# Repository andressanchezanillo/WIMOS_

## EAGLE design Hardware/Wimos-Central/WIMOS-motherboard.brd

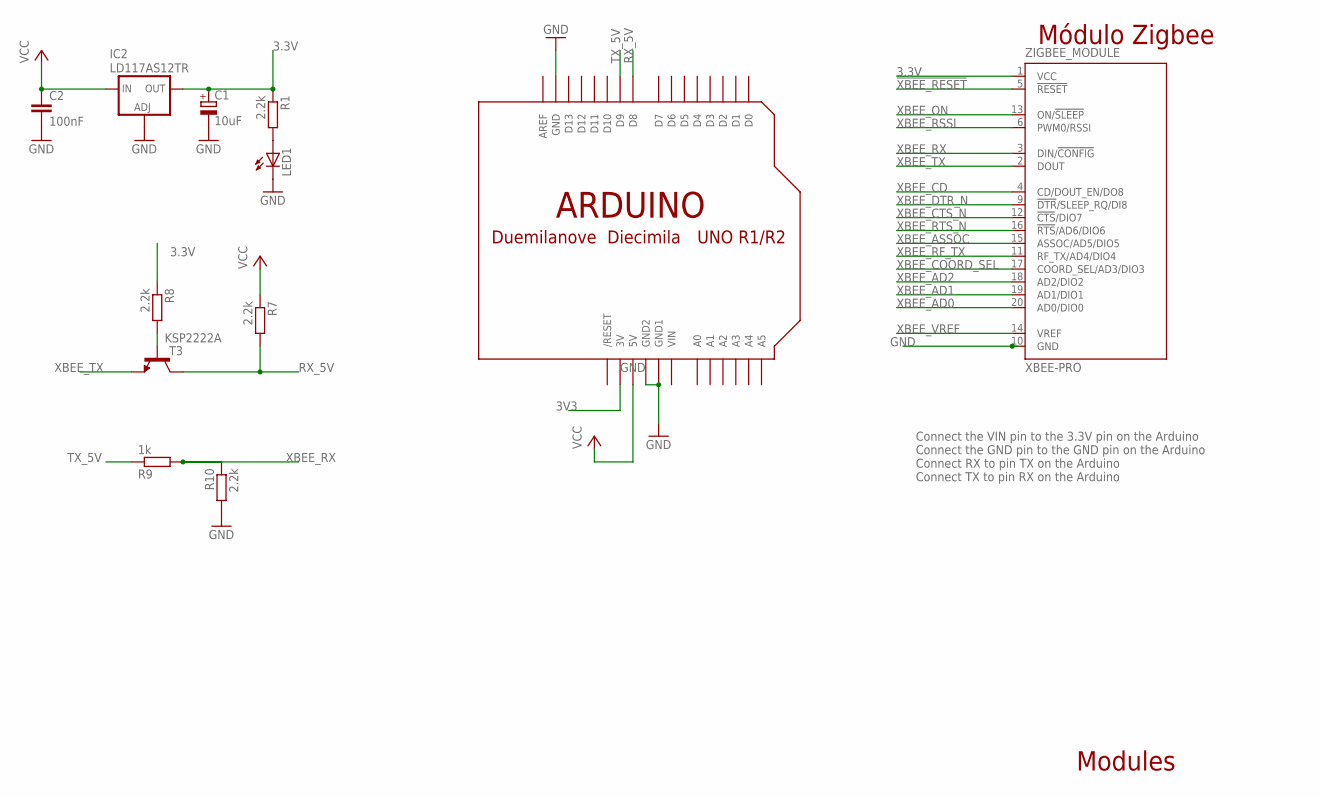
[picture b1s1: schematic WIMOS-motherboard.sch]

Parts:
C1: 10uF; 153CLV-0810
C2: 100nF; C0805K
IC2: LD117AS12TR; SOT223
LED1: LED5MM
R1: 2.2k; R0805
R7, R8, R10: 2.2k; 0204/5
R9: 1k; 0204/5
T3: KSP2222A; TO92-CBE
U$1: ARDUINO-NODIM
ZIGBEE_MODULE: XBEE-PRO

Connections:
3.3V: C1.+, IC2.4 (OUT), R1.1, R8.1, ZIGBEE_MODULE.1 (VCC)
3V3: U$1.3V
!XBEE_RESET: ZIGBEE_MODULE.5 (!RESET)
GND: C1.-, C2.2, IC2.1 (ADJ), LED1.K (C), R10.2, U$1.GND, U$1.GND1, U$1.GND2, ZIGBEE_MODULE.10 (GND)
unnamed: LED1.A, R1.2
unnamed: R8.2, T3.B
RX_5V: R7.2, T3.C, U$1.D8
TX_5V: R9.1, U$1.D9
VCC: C2.1, IC2.3 (IN), R7.1, U$1.5V
VIN: U$1.VIN
XBEE_AD0: ZIGBEE_MODULE.20 (AD0/DIO0)
XBEE_AD1: ZIGBEE_MODULE.19 (AD1/DIO1)
XBEE_AD2: ZIGBEE_MODULE.18 (AD2/DIO2)
XBEE_ASSOC: ZIGBEE_MODULE.15 (ASSOC/AD5/DIO5)
XBEE_CD: ZIGBEE_MODULE.4 (CD/DOUT_EN/DO8)
XBEE_COORD_SEL: ZIGBEE_MODULE.17 (COORD_SEL/AD3/DIO3)
XBEE_CTS_N: ZIGBEE_MODULE.12 (!CTS!/DIO7)
XBEE_DTR_N: ZIGBEE_MODULE.9 (!DTR!/SLEEP_RQ/DI8)
XBEE_ON: ZIGBEE_MODULE.13 (ON/!SLEEP)
XBEE_RF_TX: ZIGBEE_MODULE.11 (RF_TX/AD4/DIO4)
XBEE_RSSI: ZIGBEE_MODULE.6 (PWM0/RSSI)
XBEE_RTS_N: ZIGBEE_MODULE.16 (!RTS!/AD6/DIO6)
XBEE_RX: R9.2, R10.1, ZIGBEE_MODULE.3 (DIN/!CONFIG)
XBEE_TX: T3.E, ZIGBEE_MODULE.2 (DOUT)
XBEE_VREF: ZIGBEE_MODULE.14 (VREF)

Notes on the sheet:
Modules
Connect the VIN pin to the 3.3V pin on the Arduino Connect the GND pin to the GND pin on the Arduino Connect RX to pin TX on the Arduino Connect TX to pin RX on the Arduino
Módulo Zigbee

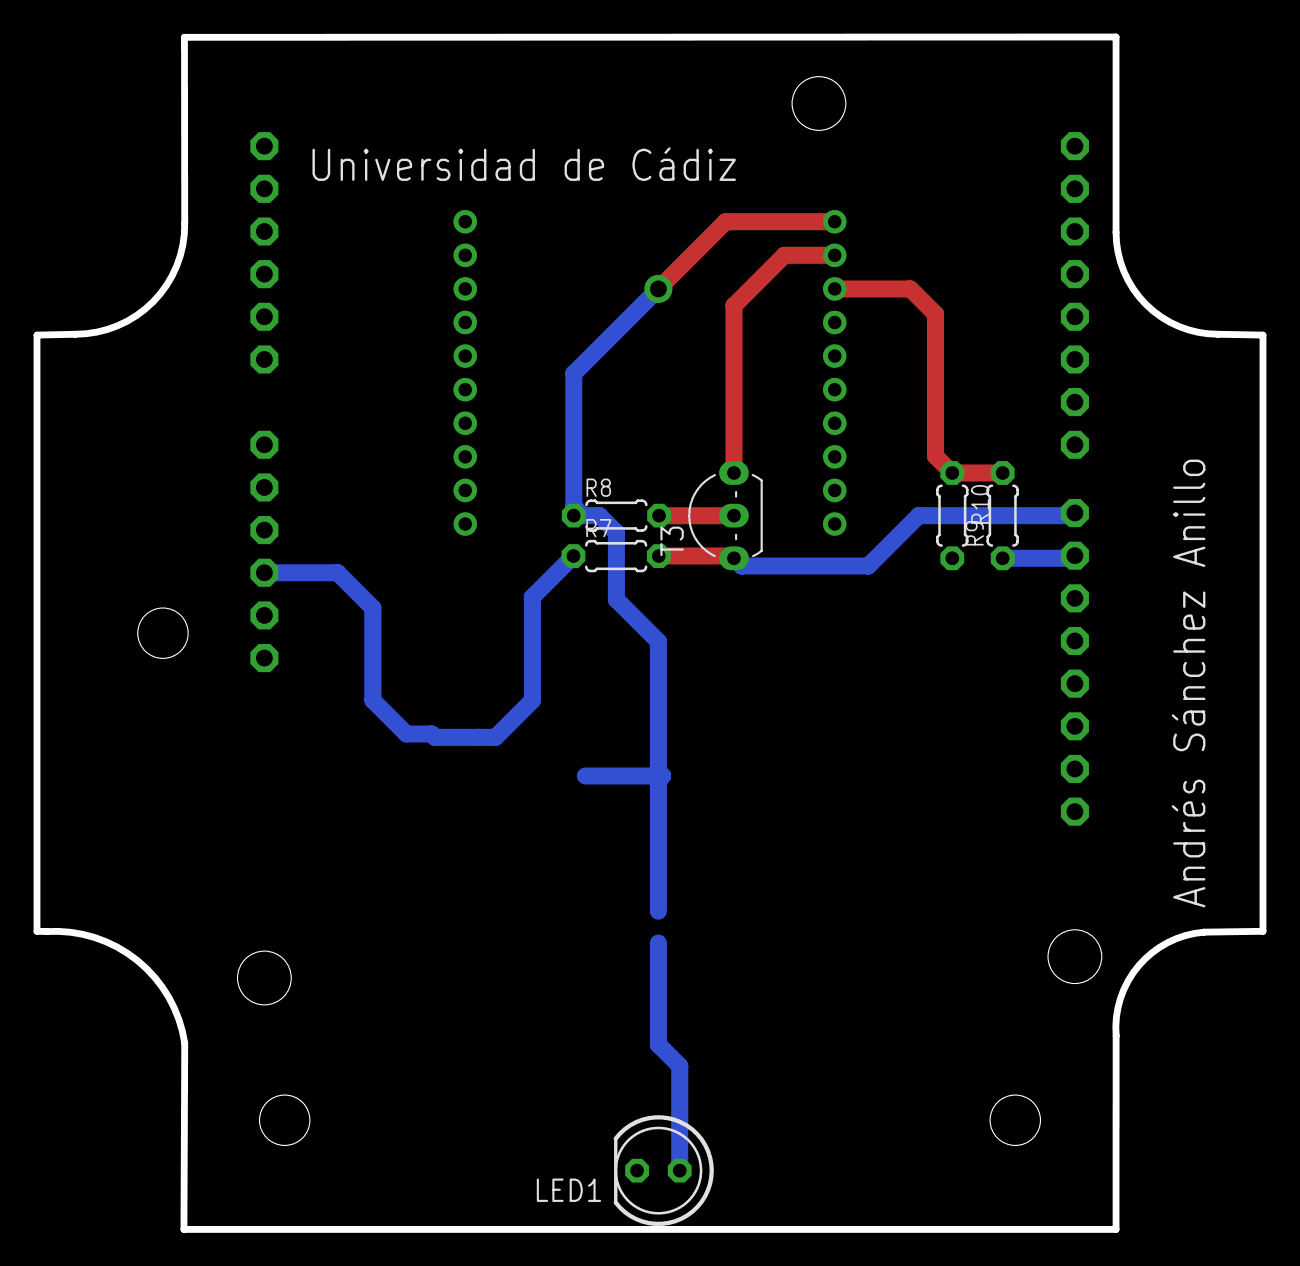
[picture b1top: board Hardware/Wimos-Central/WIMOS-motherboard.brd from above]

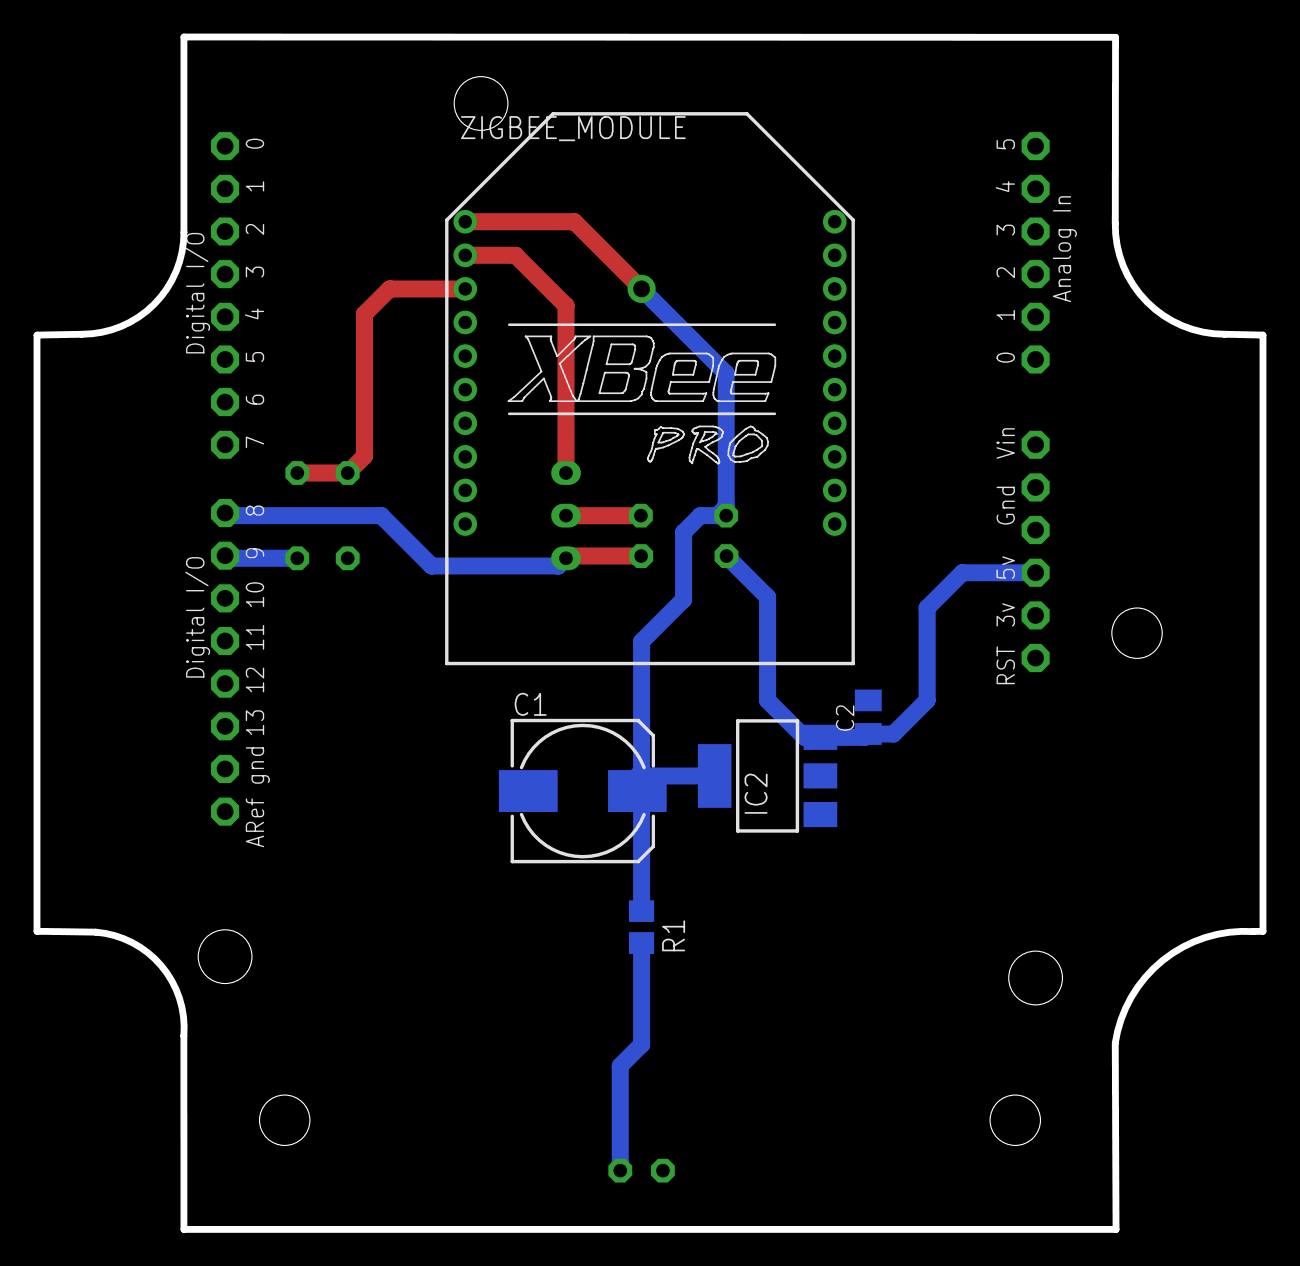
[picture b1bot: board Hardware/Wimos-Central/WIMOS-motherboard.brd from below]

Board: 2 copper layers, 73.0 x 71.0 mm, 12 parts (6 on the bottom side), 9 nets.

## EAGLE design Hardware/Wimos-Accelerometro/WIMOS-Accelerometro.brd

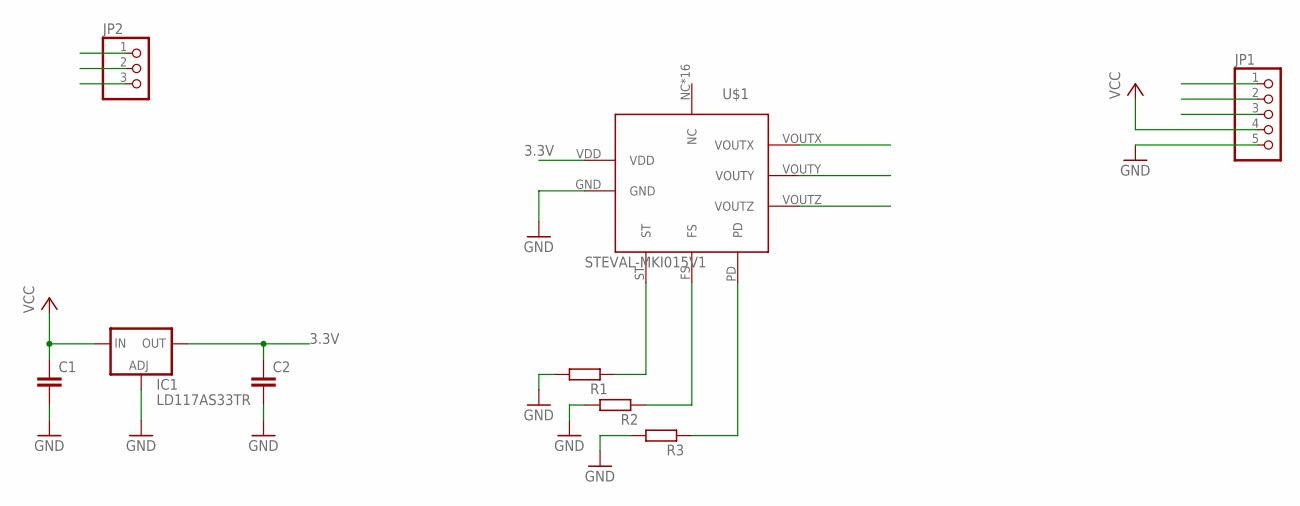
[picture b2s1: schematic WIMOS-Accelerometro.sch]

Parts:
C1, C2: C-EUC0805; C0805
IC1: LD117AS33TR; SOT223
JP1: PINHD-1X5; 1X05
JP2: PINHD-1X3; 1X03
R1, R2, R3: R-EU_R0805; R0805
U$1: STEVAL-MKI015V1

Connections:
3.3V: C2.1, IC1.4 (OUT), U$1.VDD
FS: JP2.2, R2.1, U$1.FS
GND: C1.2, C2.2, IC1.1 (ADJ), JP1.5, R1.2, R2.2, R3.2, U$1.GND
PD: JP2.3, R3.1, U$1.PD
ST: JP2.1, R1.1, U$1.ST
VCC: C1.1, IC1.3 (IN), JP1.4
VOUTX: JP1.1, U$1.VOUTX
VOUTY: JP1.2, U$1.VOUTY
VOUTZ: JP1.3, U$1.VOUTZ

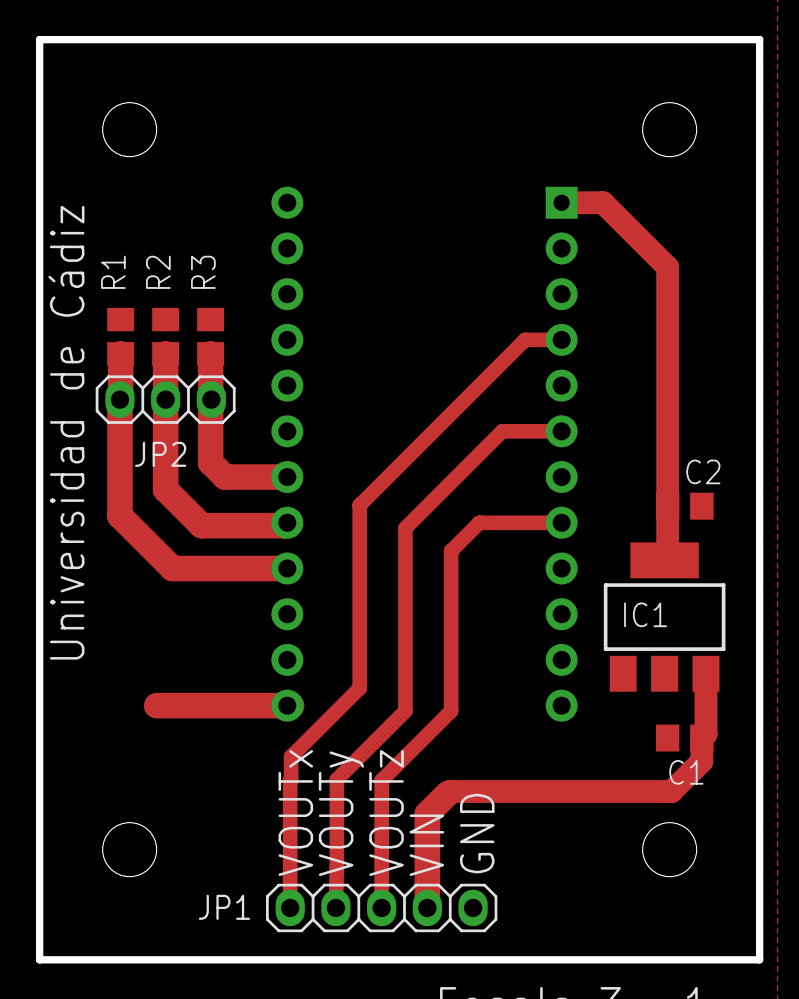
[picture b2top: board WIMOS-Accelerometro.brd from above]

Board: 2 copper layers, 40.0 x 51.1 mm, 9 parts (1 on the bottom side), 9 nets.

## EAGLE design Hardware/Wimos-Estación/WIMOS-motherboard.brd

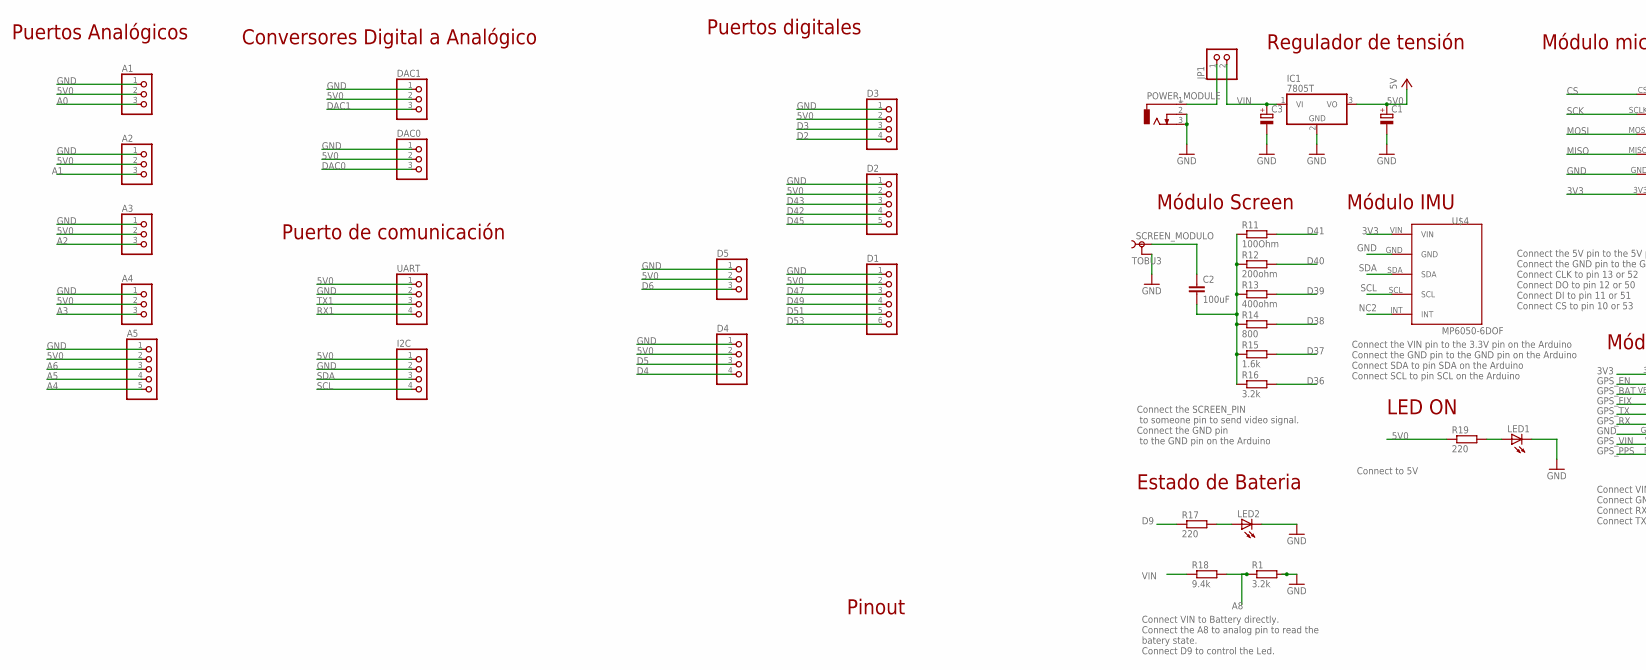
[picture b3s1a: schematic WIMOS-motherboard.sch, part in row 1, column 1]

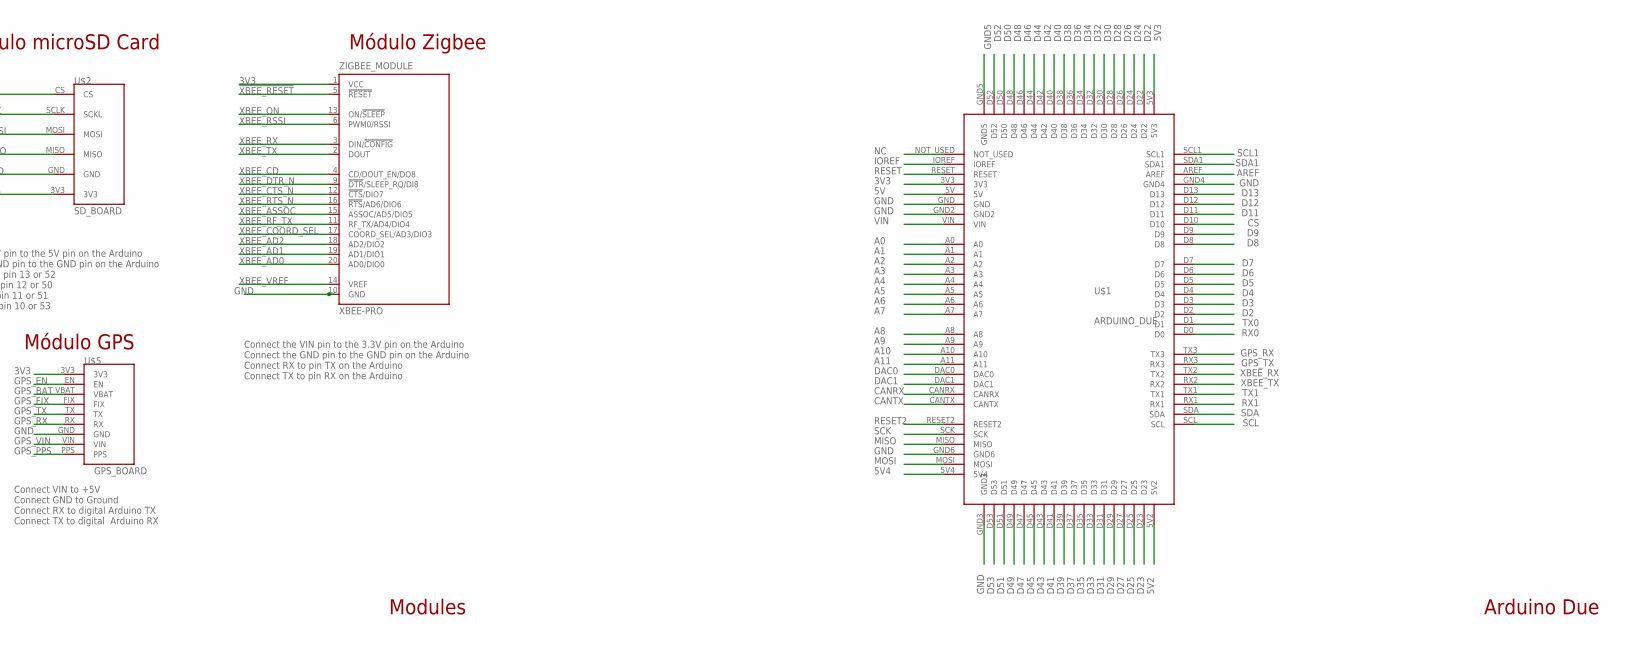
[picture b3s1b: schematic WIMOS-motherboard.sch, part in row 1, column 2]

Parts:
A1, A2, A3, A4: PINHD-1X3/90; 1X03/90
A5: PINHD-1X5/90; 1X05/90
C1, C3: CPOL-EU153CLV-0810; 153CLV-0810
C2: 100uF; C025-025X050
D1: PINHD-1X6/90; 1X06/90
D2: PINHD-1X5/90; 1X05/90
D3, D4: PINHD-1X4/90; 1X04/90
D5: PINHD-1X3/90; 1X03/90
DAC0, DAC1: PINHD-1X3/90; 1X03/90
I2C: PINHD-1X4/90; 1X04/90
IC1: 7805T; TO220H
JP1: PINHD-1X2; 1X02
LED1, LED2: LED_E; LED_1206
POWER_MODULE: DCJ0303
R1, R16: 3.2k; R0805
R11: 100Ohm; R0805
R12: 200ohm; R0805
R13: 400ohm; R0805
R14: 800; R0805
R15: 1.6k; R0805
R17, R19: 220; R0805
R18: 9.4k; R0805
SCREEN_MODULO: TOBU3
U$1: ARDUINO_DUE
U$2: SD_BOARD
U$4: MP6050-6DOF
U$5: GPS_BOARD; SD_BOARD
UART: PINHD-1X4/90; 1X04/90
ZIGBEE_MODULE: XBEE-PRO

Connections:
3V3: U$1.3V3, U$2.3V3, U$4.VIN, U$5.3V3, ZIGBEE_MODULE.1 (VCC)
5V: U$1.5V
5V0: A1.2, A2.2, A3.2, A4.2, A5.2, C1.+, D1.2, D2.2, D3.2, D4.2, D5.2, DAC0.2, DAC1.2, I2C.1, IC1.3 (VO), R19.1, UART.1
5V2: U$1.5V2
5V3: U$1.5V3
5V4: U$1.5V4
!XBEE_RESET: ZIGBEE_MODULE.5 (!RESET)
A0: A1.3, U$1.A0
A1: A2.3, U$1.A1
A2: A3.3, U$1.A2
A3: A4.3, U$1.A3
A4: A5.5, U$1.A4
A5: A5.4, U$1.A5
A6: A5.3, U$1.A6
A7: U$1.A7
A8: R1.1, R18.2, U$1.A8
A9: U$1.A9
A10: U$1.A10
A11: U$1.A11
AREF: U$1.AREF
CANRX: U$1.CANRX
CANTX: U$1.CANTX
CS: U$1.D10, U$2.CS
D2: D3.4, U$1.D2
D3: D3.3, U$1.D3
D4: D4.4, U$1.D4
D5: D4.3, U$1.D5
D6: D5.3, U$1.D6
D7: U$1.D7
D8: U$1.D8
D9: R17.1, U$1.D9
D11: U$1.D11
D12: U$1.D12
D13: U$1.D13
D22: U$1.D22
D23: U$1.D23
D24: U$1.D24
D25: U$1.D25
D26: U$1.D26
D27: U$1.D27
D28: U$1.D28
D29: U$1.D29
D30: U$1.D30
D31: U$1.D31
D32: U$1.D32
D33: U$1.D33
D34: U$1.D34
D35: U$1.D35
D36: R16.2, U$1.D36
D37: R15.2, U$1.D37
D38: R14.2, U$1.D38
D39: R13.2, U$1.D39
D40: R12.2, U$1.D40
D41: R11.2, U$1.D41
D42: D2.4, U$1.D42
D43: D2.3, U$1.D43
D44: U$1.D44
D45: D2.5, U$1.D45
D46: U$1.D46
D47: D1.3, U$1.D47
D48: U$1.D48
D49: D1.4, U$1.D49
D50: U$1.D50
D51: D1.5, U$1.D51
D52: U$1.D52
D53: D1.6, U$1.D53
DAC0: DAC0.3, U$1.DAC0
DAC1: DAC1.3, U$1.DAC1
GND: A1.1, A2.1, A3.1, A4.1, A5.1, C1.-, C3.-, D1.1, D2.1, D3.1, D4.1, D5.1, DAC0.1, DAC1.1, I2C.2, IC1.2 (GND), LED1.C, LED2.C, POWER_MODULE.2, POWER_MODULE.3, R1.2, SCREEN_MODULO.2, SCREEN_MODULO.2@1 (2), SCREEN_MODULO.2@2 (2), U$1.GND, U$1.GND2, U$1.GND3, U$1.GND4, U$1.GND6, U$2.GND, U$4.GND, U$5.GND, UART.2, ZIGBEE_MODULE.10 (GND)
GND5: U$1.GND5
GPS_BAT: U$5.VBAT
GPS_EN: U$5.EN
GPS_FIX: U$5.FIX
GPS_PPS: U$5.PPS
GPS_RX: U$1.TX3, U$5.RX
GPS_TX: U$1.RX3, U$5.TX
GPS_VIN: U$5.VIN
IOREF: U$1.IOREF
MISO: U$1.MISO, U$2.MISO
MOSI: U$1.MOSI, U$2.MOSI
unnamed: LED1.A, R19.2
unnamed: C2.1, SCREEN_MODULO.1
unnamed: JP1.1, POWER_MODULE.1
unnamed: LED2.A, R17.2
unnamed: C2.2, R11.1, R12.1, R13.1, R14.1, R15.1, R16.1
NC: U$1.NOT_USED
NC2: U$4.INT
RESET: U$1.RESET
RESET2: U$1.RESET2
RX0: U$1.D0
RX1: U$1.RX1, UART.4
SCK: U$1.SCK, U$2.SCLK (SCKL)
SCL: I2C.4, U$1.SCL, U$4.SCL
SCL1: U$1.SCL1
SDA: I2C.3, U$1.SDA, U$4.SDA
SDA1: U$1.SDA1
TX0: U$1.D1
TX1: U$1.TX1, UART.3
VIN: C3.+, IC1.1 (VI), JP1.2, R18.1, U$1.VIN
XBEE_AD0: ZIGBEE_MODULE.20 (AD0/DIO0)
XBEE_AD1: ZIGBEE_MODULE.19 (AD1/DIO1)
XBEE_AD2: ZIGBEE_MODULE.18 (AD2/DIO2)
XBEE_ASSOC: ZIGBEE_MODULE.15 (ASSOC/AD5/DIO5)
XBEE_CD: ZIGBEE_MODULE.4 (CD/DOUT_EN/DO8)
XBEE_COORD_SEL: ZIGBEE_MODULE.17 (COORD_SEL/AD3/DIO3)
XBEE_CTS_N: ZIGBEE_MODULE.12 (!CTS!/DIO7)
XBEE_DTR_N: ZIGBEE_MODULE.9 (!DTR!/SLEEP_RQ/DI8)
XBEE_ON: ZIGBEE_MODULE.13 (ON/!SLEEP)
XBEE_RF_TX: ZIGBEE_MODULE.11 (RF_TX/AD4/DIO4)
XBEE_RSSI: ZIGBEE_MODULE.6 (PWM0/RSSI)
XBEE_RTS_N: ZIGBEE_MODULE.16 (!RTS!/AD6/DIO6)
XBEE_RX: U$1.TX2, ZIGBEE_MODULE.3 (DIN/!CONFIG)
XBEE_TX: U$1.RX2, ZIGBEE_MODULE.2 (DOUT)
XBEE_VREF: ZIGBEE_MODULE.14 (VREF)

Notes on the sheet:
Connect the 5V pin to the 5V pin on the Arduino Connect the GND pin to the GND pin on the Arduino Connect CLK to pin 13 or 52 Connect DO to pin 12 or 50 Connect DI to pin 11 or 51 Connect CS to pin 10 or 53
Connect the VIN pin to the 3.3V pin on the Arduino Connect the GND pin to the GND pin on the Arduino Connect SDA to pin SDA on the Arduino Connect SCL to pin SCL on the Arduino
Connect VIN to +5V Connect GND to Ground Connect RX to digital Arduino TX Connect TX to digital Arduino RX
Connect the VIN pin to the 3.3V pin on the Arduino Connect the GND pin to the GND pin on the Arduino Connect RX to pin TX on the Arduino Connect TX to pin RX on the Arduino
Modules
Arduino Due
Pinout
Regulador de tensión
Módulo microSD Card
Módulo Zigbee
Módulo IMU
Módulo Screen
Módulo GPS
Connect the SCREEN_PIN to someone pin to send video signal. Connect the GND pin to the GND pin on the Arduino
Puertos Analógicos
Conversores Digital a Analógico
Puerto de comunicación
Puertos digitales
Estado de Bateria
LED ON
Connect to 5V
Connect VIN to Battery directly. Connect the A8 to analog pin to read the batery state. Connect D9 to control the Led.

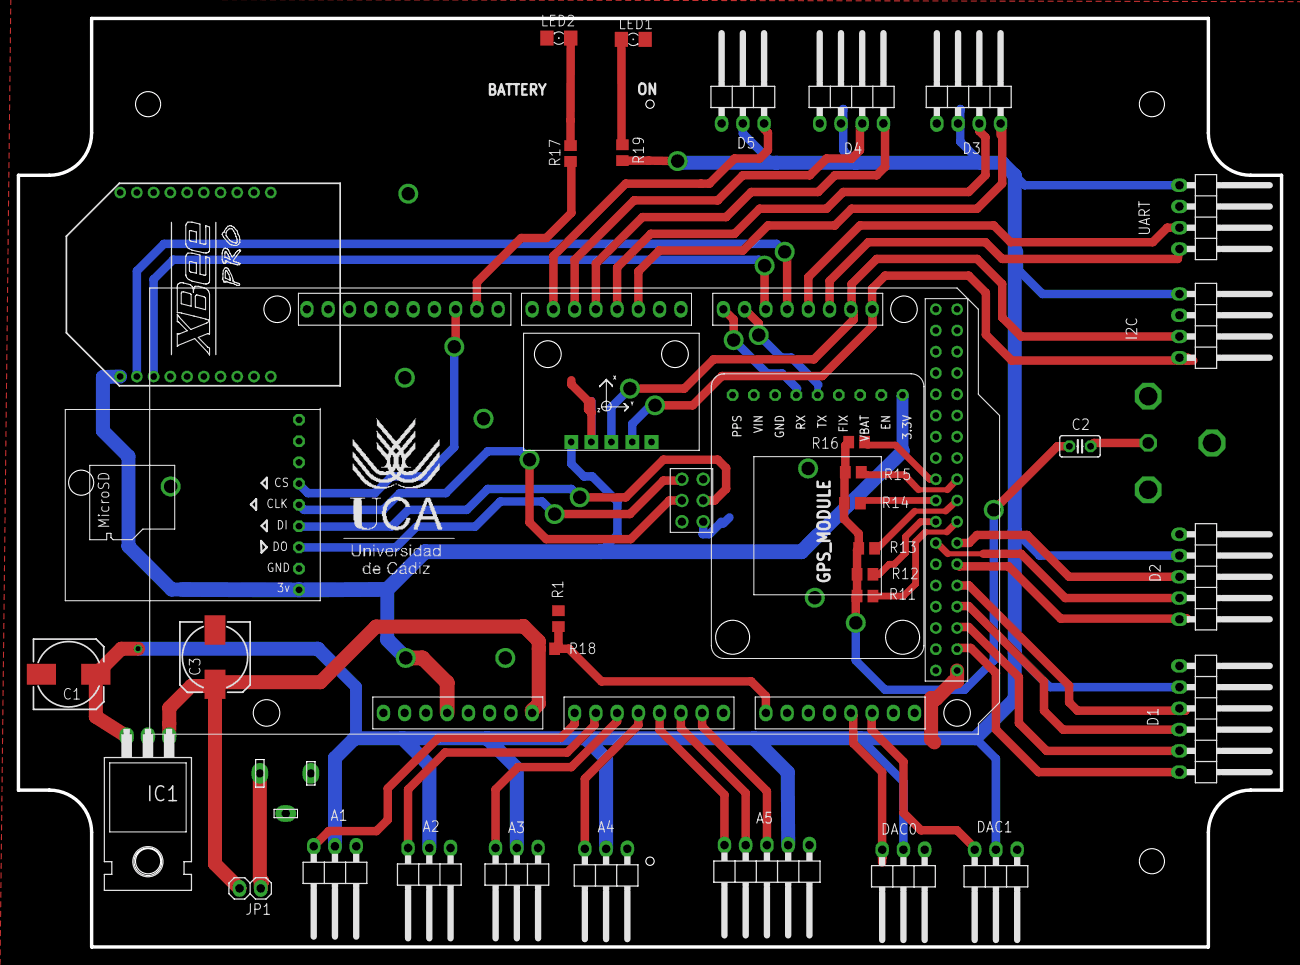
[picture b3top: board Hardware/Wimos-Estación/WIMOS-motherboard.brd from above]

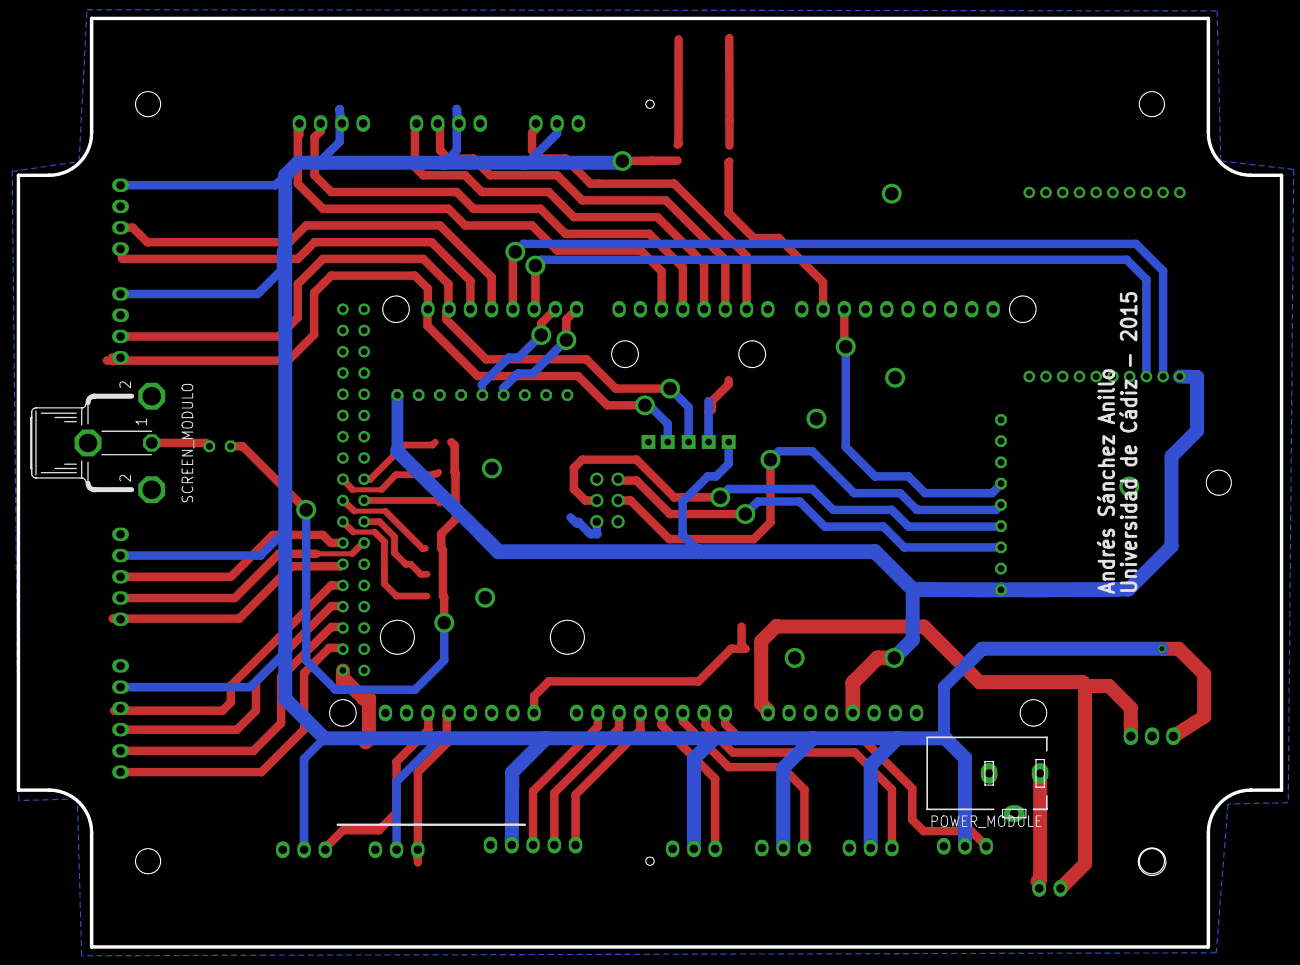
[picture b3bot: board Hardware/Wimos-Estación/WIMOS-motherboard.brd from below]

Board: 2 copper layers, 151.0 x 111.0 mm, 38 parts (2 on the bottom side), 50 nets.

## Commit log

2016-11-10 TFG
    TFG commit
2016-11-10 SW
    The last code was updated
2016-11-12 SW
    Debug interface added.
    Wimos core defined
2016-11-12 SW
    Fix Bug Debug
    GPS Time Updater
2016-11-13 SW
    GPS interface finished
2016-11-13 DOC
    Estación Sísmica updated
2016-11-13 doc
    sistema general case of uses updated
2016-11-15 DOC
    Modelo de caso de usos actualizados
2016-11-15 Doc
    MCD diagram updated
2016-11-19 DOC
    Updated the secuence diagram.
    Add States machines.
2016-11-21 Doc
    Diagrams updated and sorted by increment and step
2016-11-21 Software
    Create a Desktop Software project
2016-11-26 DOC
    Update diagrams
2016-11-26 SW
    Updated:
    - RF function,
    - TV function.
    - Battery reader.
2016-11-27 SW
    Wimos SD updated
    Wimos Debug Valid updated
2016-11-29 SW
    Update the unit test and validation test for Battery Reader
2016-12-06 SW
    Unit Testing and Validation Software
2016-12-11 SW
    Internal IMU reader implemented.
    Internal IMU Test and Validation implemented.
2016-12-11 SW
    External port reader implemented
2016-12-11 SW
    TV signal disable and this capability is erased of this branch
2016-12-15 SW
    SD testing and validation
2016-12-24 SW
    Incremento 4
2016-12-24 SW
    Debug traces
2016-12-31 SW
    RF commands implementation
2017-01-22 SW
    Communication ACK
2017-02-06 SW
    Communication finished
2017-02-06 DOC
    Communication diagrams.
2017-02-13 SW
    Communication UTs
2017-02-17 SW
    Communication 4bytes packetization.
2017-02-26 SW
    Misra C application
2017-02-26 SW
    Center Xbee configuration file
2017-03-08 SW
    Alert Increment 4
2017-03-08 SW
    QT Proyect erased
2017-03-08 SW
    PyQt proyect created
2017-03-12 SW
    Python Gui base
2017-03-13 SW
    Restructure the Desktop software
2017-03-18 SW
    Software GUI v0.1
2017-03-18 SW - Release
    Release 18/03/2017
2017-03-18 Release
    2017/03/18 - V001
2017-03-18 SW
    Software GUI Update
2017-03-18 SW
    Update GUI fixed
2017-03-22 SW
    GUI Setting Central - Host
2017-04-02 SW
    Gui Finished v1.0
2017-04-02 FW
    Fix I2C issue
2017-04-02 FW
    Fix issue
2017-04-19 FRQ05
    Tiempo de refresco de sensores y de información
2017-04-19 GUI V1.0
    Desktop GUI versión 0.
2017-04-26 GPS issue fixed
    GPS processment fixed
2017-05-07 FW
    Copyright fixed
2017-05-07 FW
    UTs - Incremento 5
2017-05-07 DOC
    Documentación Incremento 5 - 6
2017-05-07 SW
    Compilation files
2017-05-21 DOC
    Add Diagram of design and implementarion
2017-05-21 PRJ
    Clearing
2017-05-21 *** New Release 21/05/2017 **
    New release with Zip format
2017-05-21 SW
    Build proyect structure
2017-05-21 SW
    UTs VT for GUI Software
2017-05-22 SW
    UTs finished
2017-05-26 RELEASE
    Entregable con Arturo preEntrega 26/05/2017
2017-05-31 FW
    GPS issue Fixed
2017-05-31 DOC+FW
    TV output erased
2017-05-31 DOC
    Hardware deployment diagram.
2017-06-11 DOC + HW
    Doc incremento 1 y 2 (Implementación)
2017-06-26 DOC
    Documentación Final 26/06/2017
2017-07-05 Installer V1.0
    Software Installer
2017-07-05 FW
    Fixing Timming INFO frame
    Fixing Checksum Builder
    Fixing MSG parameters RunFunction
2017-07-14 FW
    SD controller
2017-07-14 DOC
    new image
2017-07-15 FW
    UTs Fixing.
2017-08-03 TFG
    Last Commit
